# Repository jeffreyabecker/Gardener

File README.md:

# Gardener

An ESP32 vacuum pump controller. It pulls a chamber to a target depth below ambient, holds it,
then vents it — driven over a web page and a Bluetooth link.

The web page and the Bluetooth link are the ways in. A controller sets a depth and the machine
pulls to it; a vent releases the chamber; a reset clears a fault. What the device owns is what has
to happen when nobody is watching: holding the target, and venting the chamber through one path on
stop, abort or fault. Pressures are kPa below ambient, on every link and in the firmware.

The device is the machine — pump, sensor and vent valve. One sketch,
[firmware/gardener](./firmware/gardener), composes the libraries for it: what it names is what the
device has, over the web and Bluetooth links it builds. The USB port carries the boot and run log
and the upload, not a command interface.

## Web

The sketch joins a WiFi network, or runs its own setup access point when it has none to join, and
serves a page tree at `/` and the HTTP API under `/api`:

| call | result |
| --- | --- |
| `GET /api/status` | `{"uptime_ms":…,"pressure_kpa":20.5,"target":30,"state":"HOLD","hold_time_ms":1000,"duty":100,"fault":"none","device_id":"E072A1234CD0"}` |
| `POST /api/set` with `{"target":30}` or `{"target":"-"}` | `{"target":30,"state":"PULL"}`, or `{"target":0,"state":"VENT"}` |
| `POST /api/vent` | `{"state":"VENT"}` |
| `POST /api/reset` | `{"state":"IDLE"}` |
| `GET /api/wifi` | `{"ssid":"…","mode":"sta","ip":"192.168.1.51","keep_ap":false}` |
| `GET /api/wifi/scan` | `{"networks":[{"ssid":"…","rssi":-51},…]}` |
| `POST /api/wifi` with `{"ssid":"…","pass":"…","keep_ap":false}` | `204`, no body |
| `POST /api/wifi/forget` | `204`, no body |

Requests and results are both `application/json`, built and parsed with the cJSON that ships inside
the ESP32 core. The status code is the outcome: 200 for a call the machine took, 204 for one with
nothing to return, 400 for a refused argument, 409 for a set the machine will not take and 404 for a
missing page. A refusal is an object with an `error` member and a `reason`, `value`, `min` or `max`
beside it; a success is an object of the fields the call answers with. Every status call ends with
`device_id`, the board's 48-bit station MAC as twelve hex digits, so the Settings page can say which
board it is.

On first boot there is no stored network, so the board starts an access point and a captive portal;
joining it opens the page. Scan, pick a network, enter its password and save. The board joins it,
and unless **keep the setup network on** is ticked the access point closes once the join succeeds.
**Forget** clears the stored network and brings the portal back. The serial log prints the portal
name, the join attempts and the address the board ends up on. The page and the API are
unauthenticated on whatever network the board joins, so anyone who can reach the board can command
it.

The setup network is the board, not a network it joins, and its name and key come out of the same
config file: `ap_ssid` and `ap_pass` in `/wifi.conf`, which the image carries from
`firmware/gardener/data/wifi.conf`. With no file, the board names itself `Gardener-<suffix>` — the
prefix knob and the tail of its MAC, so two boards on a bench still differ — and the password knob
decides whether it is open. A name is used verbatim up to 32 characters, and a password is 8 to 63
characters or nothing: anything else is logged at boot and the portal comes up open, rather than
with a key nobody can type. Start from
[wifi.conf.example](./firmware/gardener/wifi.conf.example), which documents every field; the real
file is not committed, because a password does not belong in the tree.

The board answers mDNS on whichever interface is up, under the setup network's name in lower case:
`http://gardener-<suffix>.local/` is the page when the board named itself, and a rig whose
`ap_ssid` is its own answers as that name lowered, so `Bench-3` is `bench-3.local`. The API is
advertised as `_gardener._tcp` on the same port with an `api=/api` TXT record, beside `_http._tcp`
for the page. A client that joined the access point can use the name as well as the address, so the
page is reachable before any address is known.

The page is a file tree on the board, not a string in the firmware: everything under
[firmware/gardener/data/www](./firmware/gardener/data/www) becomes the LittleFS image that
`--task data` builds, and a `GET` is the matching path inside it — `/` and `/dir/` serve that
directory's `index.html`, `/page.css` serves the stylesheet beside it, and a URI with `..` in it is
refused. A file added to the folder is a URL, and the folder splits the device in two: `/` is the
machine's readings and its three buttons, and `/settings.html` is the board's own ID and the
network — what the radio sees, what it joined, and the choice it stores — and a nav bar at the top
of each says which page is which and links to the other. `page.css` and `app.js` are shared;
`machine.js` and `settings.js` are each page's own. A `GET` that matches nothing is the portal's
landing while the setup access point is up and the page tree's `404.html` otherwise; a path under
`/api` that matches nothing answers `404 {"error":"not_found"}`. A board whose image will not mount
has no `404.html` to serve, answers a plain 404, and says so in the boot log.

The network the board stores lives in the same partition, at `/wifi.conf` outside `www`, as one
JSON object the page's own save writes. It is not reachable over HTTP, and it is cleared by a new
image: re-flashing the page tree brings the setup access point back. A file written by a firmware
that spoke form encoding is not readable, so the first boot of this firmware comes up as its own
access point once.

## Bluetooth

A phone or a laptop beside the rig can reach the machine over Bluetooth LE without a network or an
address, in a build with the `c3-wifi-ble` or `s3-wifi-ble` profile; the default build leaves the
stack out. The
device
advertises as `Gardener-<suffix>`, the suffix being the low two bytes of its own address, and serves
one GATT service over the same control the page asks. Every characteristic requires an
encrypted, bonded link.

| what | UUID | properties |
| --- | --- | --- |
| service | `6d3a0000-6a3f-4d1c-9d5b-9e0f4c7a2b31` | — |
| status | `6d3a0001-6a3f-4d1c-9d5b-9e0f4c7a2b31` | read, notify |
| command | `6d3a0002-6a3f-4d1c-9d5b-9e0f4c7a2b31` | write |
| reply | `6d3a0003-6a3f-4d1c-9d5b-9e0f4c7a2b31` | read, notify |

Everything is little-endian, and floats are IEEE-754 binary32.

**Status** — 22 bytes, readable at any time and notified every five seconds and at once when the
state or the target moves. The hold time is appended, so a client that reads only the first 18
bytes still finds every field where it was.

| offset | size | field |
| --- | --- | --- |
| 0 | 4 | `uptime_ms` — milliseconds since boot when the reading was copied |
| 4 | 4 | `pressure_kpa` — depth below ambient, 0 at ambient |
| 8 | 4 | `target` — depth below ambient, 0 is the ambient target |
| 12 | 4 | `duty_percent` |
| 16 | 1 | `state` — 0 idle, 1 pull, 2 hold, 3 vent, 4 fault |
| 17 | 1 | `fault` — the code table below, 0 when nothing is latched |
| 18 | 4 | `hold_time_ms` — milliseconds since the state entered `HOLD`, 0 while it is not holding |

**Command** — a write with a response: one byte for `vent` and `reset`, five for `set`.

| offset | size | field |
| --- | --- | --- |
| 0 | 1 | `op` — 1 set, 2 vent, 3 reset |
| 1 | 4 | `target_kpa` — only when `op` is 1 |

**Reply** — two bytes, notified when the write is served and readable afterwards.

| offset | size | field |
| --- | --- | --- |
| 0 | 1 | `result` — 0 ok, 1 released, 2 below range, 3 above range, 4 not ready, 5 bad command |
| 1 | 1 | `refusal` — 0 none, 1 latch, 2 no reading, 3 unknown |

The codes are the machine's words written as numbers:

| fault | code | | refusal | code |
| --- | --- | --- | --- | --- |
| nothing latched | 0 | | nothing | 0 |
| `sensor` | 1 | | `latch` | 1 |
| `vent_timeout` | 2 | | `no_reading` | 2 |
| `overshoot` | 3 | | anything else | 3 |
| `no_progress` | 4 | | | |
| anything else | 5 | | | |

A write of any other length or opcode answers `bad command` and queues nothing, and so does a
five-byte `vent` or `reset`: each command has one spelling. `set` is the machine's one command and
answers what `sys set` answers — a target of 0 is `released`, and a refusal queues nothing.

One client at a time: a second is refused while the first is connected, and the board advertises
again on disconnect. Pairing is Just Works with the bond remembered, in NVS across a power cut. It
buys an encrypted link and a phone that reconnects without asking, and it authenticates nobody — the
first client to pair gets the bond, and there is no button on the board to withdraw it.

## Build

Requires `arduino-cli` with the ESP32 core, and Python 3 for the wrapper.

```powershell
arduino-cli core install esp32:esp32
python scripts/arduino.py --task build
python scripts/arduino.py --task upload --port COM5
python scripts/arduino.py --task data --port COM5
python scripts/arduino.py --task monitor --port COM5
python scripts/arduino.py --task info
```

`--task info` prints what a build is made of without touching a board: the profile, the board that
profile's FQBN pins, the flash layout that board's partition scheme cuts, and the options the
profile records.

`--task upload` writes the page image as well as the sketch, and `--task data` writes the image on
its own. The image is built with the core's `mklittlefs` and written with its `esptool` at the
offset the board's own partition table gives the `spiffs` partition, so a different scheme needs no
edit here. The write is skipped while `data/` is unchanged, since the partition also holds the
stored network; a page edit rewrites it and the board comes back as its access point. A board that
should be provisioned with its own setup network name and password needs its `data/wifi.conf` in
place before this runs — it is not committed, and `wifi.conf.example` beside the sketch is the
template.

The firmware builds for two boards, and
[firmware/gardener/sketch.yaml](./firmware/gardener/sketch.yaml) is where each one's pins and
options sit. The ESP32-C3 Super Mini puts the sensor on GPIO0, the pump on GPIO1 and the valve on
GPIO3; the ESP32-S3 puts them on GPIO10, GPIO8 and GPIO9. Every profile names `CDCOnBoot=cdc`,
which puts `Serial` on the chip's own USB CDC and without which it is UART0 and a USB cable sees
nothing. The build compiles the `c3-wifi` profile there, which pins the platform and
[libraries/Gardener](./libraries/Gardener) — the machine, the control law, the web link and the
three drivers that fill its parts — by path. `--profile s3-wifi` compiles the S3 rig instead, and
either board's `-ble` profile, `c3-wifi-ble` or `s3-wifi-ble`, adds NimBLE-Arduino 2.5.1, the
one library the tree does not hold, and with it the Bluetooth link; the sketch's `build_opt.h` sets
NimBLE's one-client connection limit in that build. Without the stack the link compiles to a stub,
because `BleLink.h` asks for the stack's headers rather than a define. The board it runs on sits beside the sketch in
[firmware/gardener](./firmware/gardener): the composition root, the parts builder, the web link, the
Bluetooth link and the tasks that drive them. The web link uses the ESP-IDF HTTP server,
`DNSServer`, `LittleFS` and `ESPmDNS` from the core, so it brings no extra library; the Bluetooth
link is the one that does.

A build keeps its object files in `firmware/gardener/build/compile-<hash>`, a path per profile and
board, so the next one compiles only what changed since, header dependents included.

The build's options are written to a generated `firmware/gardener/options.h` rather than passed as
compiler flags, so changing one recompiles the files that read it and nothing else. Each profile in
[firmware/gardener/sketch.yaml](./firmware/gardener/sketch.yaml) records its build's options under
`defines:`, one `NAME: value` per line — the pins the sketch wires its parts to, the core the S3's
control tick takes, then the numbers a different pump or valve changes. The script
[scripts/arduino.py](./scripts/arduino.py) reads the selected profile's block and writes it into the
header; `--define` overrides one for a single run.
The header `core/knob_defaults.h` beside `core/Knob.h` is generated the same way, by `tools/knob.py`
from the `GARDENER_KNOB_VALID` calls, and both build paths write it before they compile.

## Unit tests

The tree's own C++ runs on the host, with no board and no data image:

```powershell
python tools/unit/check.py                        # build and run every case
python tools/unit/check.py --list-test-cases      # what the suite holds
python tools/unit/check.py --test-case="a name"   # one case, while a change is being made
```

The suite compiles [libraries/Gardener](./libraries/Gardener) beside its own cases under
[doctest](./tools/doctest), with [tools/host](./tools/host) supplying the Arduino API it is built
against and a clock a case advances. It needs a C++ compiler (`g++` or `clang++`) and Python, and
nothing else.

## Formatting

The C++ is formatted with `clang-format` from [.clang-format](./.clang-format) at the root, which
holds the style [.github/skills/cpp](./.github/skills/cpp/SKILL.md) describes: two spaces, a brace on
the statement's own line, a hundred columns, and comments left as they were written.

```powershell
clang-format -i (git ls-files '*.h' '*.cpp' '*.ino')   # rewrite what is not formatted
clang-format --dry-run --Werror libraries/Gardener/src/machine/Machine.h
```

What keeps another style carries a `.clang-format` of its own switching formatting off — doctest,
and the host's Arduino core and stand-ins — so the sweep leaves them alone. An editor reads the
same files, so a save lands in the shape the sweep would give it.

## Documentation

- [docs/README.md](./docs/README.md) — the index: specs, guides and backlogs
- [docs/guides/poc-parts.md](./docs/guides/poc-parts.md) — the parts, the wiring and a build
- [docs/guides/web-api.md](./docs/guides/web-api.md) — the HTTP API, the page tree and network
  provisioning
- [docs/archive/specs-and-plans.zip](./docs/archive/specs-and-plans.zip) — every spec and plan as it
  stood before the panel port, kept for reference and read by nothing

## Safety

Vacuum work is not benign: imploding chambers, collapsing tubing and pumped liquids or vapours can
hurt people and destroy hardware. Keep a rated catch pot and filter in line, and remember that the
firmware's limits are software limits only.

The one hardware guarantee is the valve. It is normally open, so losing power releases the chamber
whether or not the firmware noticed; a normally closed part trades that fail-safe for holding the
vacuum through a power loss.

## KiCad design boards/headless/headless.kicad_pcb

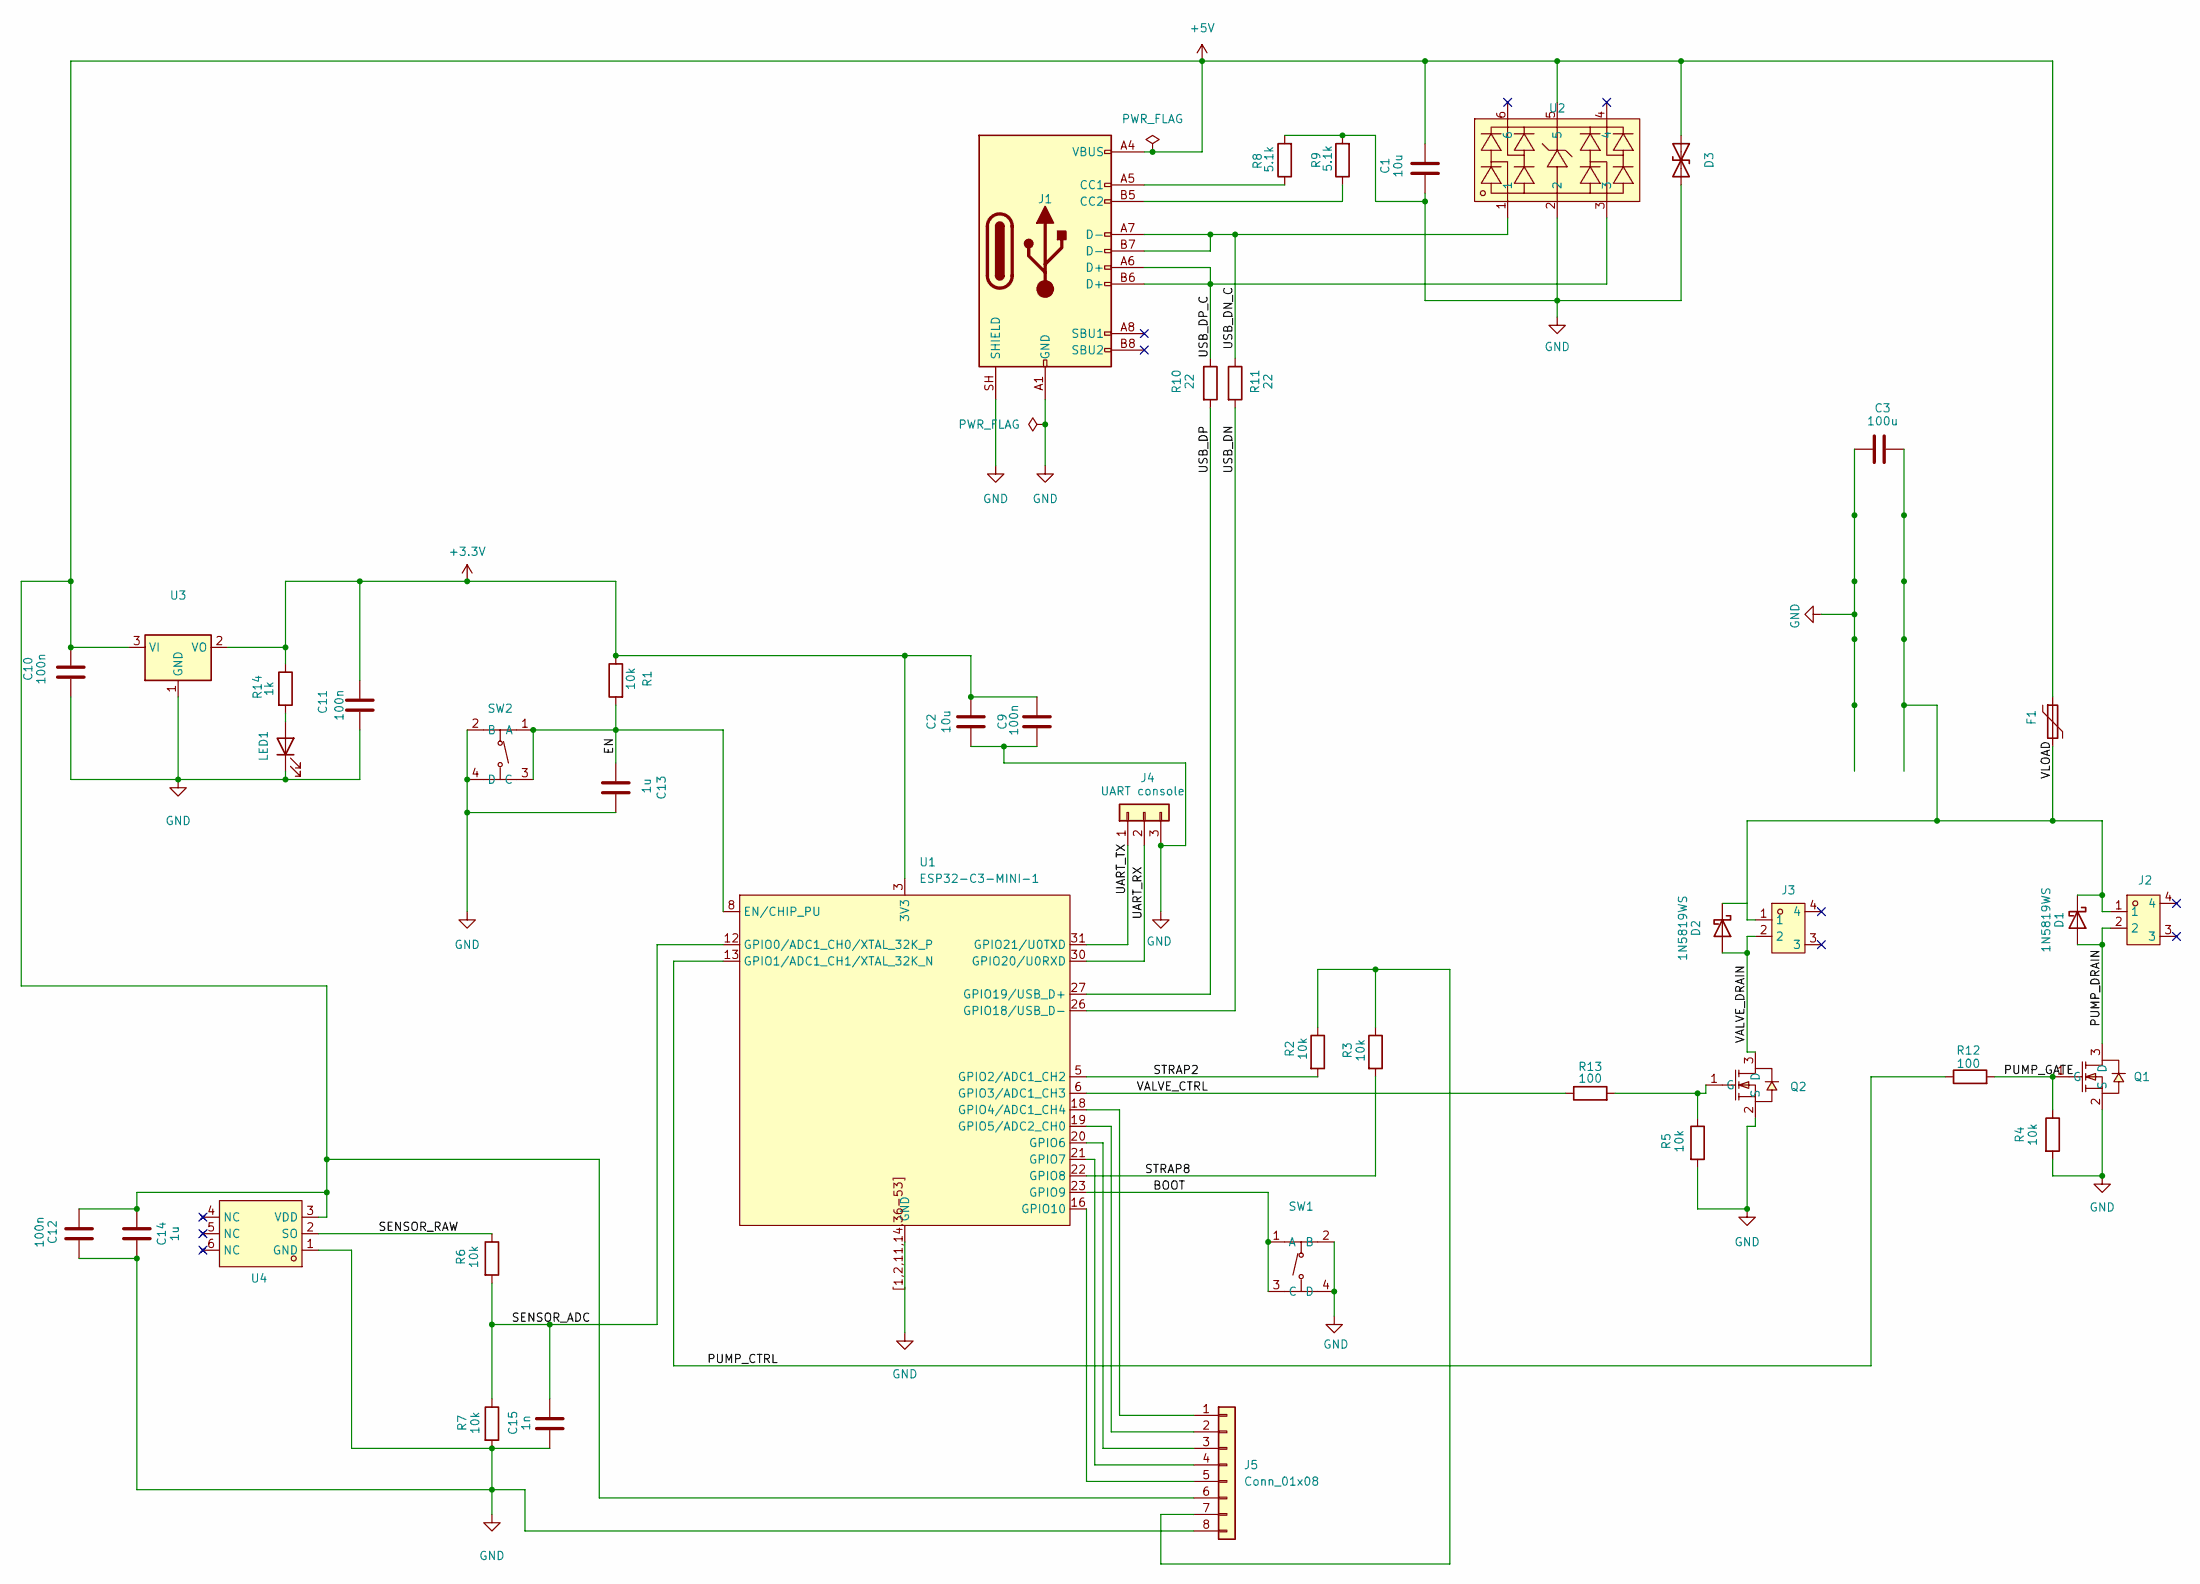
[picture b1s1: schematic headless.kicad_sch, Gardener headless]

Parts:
C1, C2: 10u; C_0805_2012Metric
C3: 100u; C_1210_3225Metric
C9, C10, C11, C12: 100n; C_0402_1005Metric
C13, C14: 1u; C_0603_1608Metric
C15: 1n; C_0603_1608Metric
D1, D2: 1N5819WS; D_SOD-323
D3: SMBJ6.5CA; D_SMB
F1: BSMD1206-110-16V; Fuse_1206_3216Metric
J1: TYPE-C-31-M-12; USB_C_Receptacle_HRO_TYPE-C-31-M-12
J2: pump; CONN-SMD_XH-2P
J3: valve; CONN-SMD_XH-2P
J4: UART console; PinHeader_1x03_P2.54mm_Vertical
J5: Conn_01x08; PinHeader_1x08_P2.54mm_Vertical
LED1: NCD0805R1; LED_0805_2012Metric
Q1, Q2: AO3400A; SOT-23
R1, R2, R3, R4, R5, R6, R7: 10k; R_0603_1608Metric
R8, R9: 5.1k; R_0603_1608Metric
R10, R11: 22; R_0603_1608Metric
R12, R13: 100; R_0603_1608Metric
R14: 1k; R_0603_1608Metric
SW1, SW2: TS-1187A-B-A-B; SW-SMD_4P-L5.1-W5.1-P3.70-LS6.5-TL_H1.5
U1: ESP32-C3-MINI-1
U2: TPUSBLC6-4SC6; SOT-23-6
U3: AMS1117-3.3; SOT-223-3_TabPin2
U4: WF100E 1BG S6 DA 0.2N4.7 AT; SOP-6_L7.0-W7.0-P2.54-LS10.3-TL-CW

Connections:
+3.3V: C2.1, C9.1, C11.1, R1.1, R14.1, U1.3 (3V3), U3.2 (VO)
+5V: C1.1, C10.1, C12.1, C14.1, D3.1 (A1), F1.1, J1.A4 (VBUS), J1.A9 (VBUS), J1.B4 (VBUS), J1.B9 (VBUS), J5.6, U2.5, U3.3 (VI), U4.3 (VDD)
/BOOT: SW1.1 (A), SW1.3 (C), U1.23 (GPIO9)
/EN: C13.1, R1.2, SW2.1 (A), SW2.3 (C), U1.8 (EN/CHIP_PU)
/PUMP_CTRL: R12.1, U1.13 (GPIO1/ADC1_CH1/XTAL_32K_N)
/PUMP_DRAIN: D1.2 (A), J2.2, Q1.3 (D)
/PUMP_GATE: Q1.1 (G), R4.1, R12.2
/SENSOR_ADC: C15.1, R6.2, R7.1, U1.12 (GPIO0/ADC1_CH0/XTAL_32K_P)
/SENSOR_RAW: R6.1, U4.2 (SO)
/STRAP2: R2.2, U1.5 (GPIO2/ADC1_CH2)
/STRAP8: R3.2, U1.22 (GPIO8)
/UART_RX: J4.2, U1.30 (GPIO20/U0RXD)
/UART_TX: J4.1, U1.31 (GPIO21/U0TXD)
/USB_DN: R11.2, U1.26 (GPIO18/USB_D-)
/USB_DN_C: J1.A7 (D-), J1.B7 (D-), R11.1, U2.1
/USB_DP: R10.2, U1.27 (GPIO19/USB_D+)
/USB_DP_C: J1.A6 (D+), J1.B6 (D+), R10.1, U2.3
/VALVE_CTRL: R13.1, U1.6 (GPIO3/ADC1_CH3)
/VALVE_DRAIN: D2.2 (A), J3.2, Q2.3 (D)
/VLOAD: C3.1, D1.1 (K), D2.1 (K), F1.2, J2.1, J3.1
GND: C1.2, C2.2, C3.2, C9.2, C10.2, C11.2, C12.2, C13.2, C14.2, C15.2, D3.2 (A2), J1.A1 (GND), J1.A12 (GND), J1.B1 (GND), J1.B12 (GND), J1.SH (SHIELD), J4.3, J5.8, LED1.1 (K), Q1.2 (S), Q2.2 (S), R4.2, R5.2, R7.2, R8.2, R9.2, SW1.2 (B), SW1.4 (D), SW2.2 (B), SW2.4 (D), U1.1 (GND), U1.2 (GND), U1.11 (GND), U1.14 (GND), U1.36 (GND), U1.37 (GND), U1.38 (GND), U1.39 (GND), U1.40 (GND), U1.41 (GND), U1.42 (GND), U1.43 (GND), U1.44 (GND), U1.45 (GND), U1.46 (GND), U1.47 (GND), U1.48 (GND), U1.49 (GND), U1.50 (GND), U1.51 (GND), U1.52 (GND), U1.53 (GND), U1.[1,2,11,14,36-53] (GND), U2.2, U3.1 (GND), U4.1 (GND)
unnamed: J1.A5 (CC1), R8.1
unnamed: J1.B5 (CC2), R9.1
unnamed: J5.1, U1.18 (GPIO4/ADC1_CH4)
unnamed: J5.2, U1.19 (GPIO5/ADC2_CH0)
unnamed: J5.3, U1.20 (GPIO6)
unnamed: J5.4, U1.21 (GPIO7)
unnamed: J5.5, U1.16 (GPIO10)
unnamed: J5.7, R2.1, R3.1
unnamed: LED1.2 (A), R14.2
unnamed: Q2.1 (G), R5.1, R13.2

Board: 2 copper layers, 42 parts (0 on the bottom side), 31 nets, no tracks yet.

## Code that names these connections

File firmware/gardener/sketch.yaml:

# The board a build compiles for, which every profile pins, and the profile a build compiles when
# none is asked for. scripts/arduino.py reads the selected profile's fqbn to ask for the partition
# table the page image is written with, so a build and its image describe the same flash.
#
# Two boards are built for, and each needs its USB options spelled out. On the S3, USBMode=hwcdc
# routes USB to the chip's USB-Serial-JTAG CDC, which is the peripheral on GPIO19/20 that both the
# ROM downloader and the sketch share. The C3 has one USB peripheral and no option to choose it
# with: the USB-Serial-JTAG CDC on GPIO18/19 is the only USB the chip has. CDCOnBoot=cdc is not
# optional on either: it maps Serial to that CDC, so the boot and run log and esptool uploads share
# one cable. Without it Serial is UART0 — on GPIO43/44
# on the S3 and on GPIO21/20 on the C3 — and the interface never reaches the USB-C socket.
#
# FlashSize and PartitionScheme pin the layout a build and its image are made for, rather than
# leaving it to whatever the board manager was set to: the platform's 4 MB default table, whose
# spiffs row is the partition `--task data` writes the page image to.
default_profile: c3-wifi

# The profiles the wrapper compiles. Each pins the board, the platform and the tree's own library by
# path, for the same reason: the build is the tree's choice rather than whatever the machine's
# library manager was left holding. A profile build excludes the globally installed libraries, so
# everything it needs is named here.
#
# Each records the build's options under `defines:`, one `NAME: value` per line, where a name is a
# knob's token without its `GARDENER_` prefix: the board's pins, the core its control tick takes,
# then the numbers a different pump or valve changes. arduino-cli has no such field and ignores the
# block, and its own `profile create` and `profile lib` commands rewrite this file without it, so
# the block is kept by hand, and a board's two profiles record the same options.
#
# The pins are the board's, and each profile's block is its own board's. On the Super Mini they are
# three of the four it breaks out with no other duty: GPIO0 is the ADC the sensor's output is read
# on, and GPIO1 and GPIO3 drive the pump and the valve. On the S3 they are GPIO10 for the sensor and
# GPIO8 and GPIO9 for the pump and the valve. The C3 has one core, so its profiles leave every task
# on core 0; the S3 keeps the control tick alone on core 1, which its profiles record.
#
# Four profiles, a board each: `c3-wifi` and `s3-wifi` are the web device with no library the tree
# does not hold, and each board's `-ble` profile is the same firmware plus the Bluetooth stack, that
# library. `c3-wifi` is the default. The link compiles to a stub in a build without the stack
# because BleLink.h looks for the stack's headers rather than a define.
profiles:
  c3-wifi-ble:
    fqbn: esp32:esp32:esp32c3:CDCOnBoot=cdc,FlashSize=4M,PartitionScheme=default
    defines:
      PIN_SENSOR_ADC: 0
      PIN_PUMP: 1
      PIN_VENT_VALVE: 3
    platforms:
      - platform: esp32:esp32 (3.0.3)
        platform_index_url: https://raw.githubusercontent.com/espressif/arduino-esp32/gh-pages/package_esp32_index.json
    libraries:
      - dir: ../../libraries/Gardener
      - NimBLE-Arduino (2.5.1)
  c3-wifi:
    fqbn: esp32:esp32:esp32c3:CDCOnBoot=cdc,FlashSize=4M,PartitionScheme=default
    defines:
      PIN_SENSOR_ADC: 0
      PIN_PUMP: 1
      PIN_VENT_VALVE: 3
    platforms:
      - platform: esp32:esp32 (3.0.3)
        platform_index_url: https://raw.githubusercontent.com/espressif/arduino-esp32/gh-pages/package_esp32_index.json
    libraries:
      - dir: ../../libraries/Gardener
  s3-wifi-ble:
    fqbn: esp32:esp32:esp32s3:USBMode=hwcdc,CDCOnBoot=cdc,FlashSize=4M,PartitionScheme=default
    defines:
      PIN_SENSOR_ADC: 10
      PIN_PUMP: 8
      PIN_VENT_VALVE: 9
      CONTROL_TASK_CORE: 1
    platforms:
      - platform: esp32:esp32 (3.0.3)
        platform_index_url: https://raw.githubusercontent.com/espressif/arduino-esp32/gh-pages/package_esp32_index.json
    libraries:
      - dir: ../../libraries/Gardener
      - NimBLE-Arduino (2.5.1)
  s3-wifi:
    fqbn: esp32:esp32:esp32s3:USBMode=hwcdc,CDCOnBoot=cdc,FlashSize=4M,PartitionScheme=default
    defines:
      PIN_SENSOR_ADC: 10
      PIN_PUMP: 8
      PIN_VENT_VALVE: 9
      CONTROL_TASK_CORE: 1
    platforms:
      - platform: esp32:esp32 (3.0.3)
        platform_index_url: https://raw.githubusercontent.com/espressif/arduino-esp32/gh-pages/package_esp32_index.json
    libraries:
      - dir: ../../libraries/Gardener
